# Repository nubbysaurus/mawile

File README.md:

# mawile
Testing the limits of a single I<sup>2</sup>C bus.

## updates
* MKII : separating ADCs into a single boards / ADC; see eevee for more information.

## summary
This repo contains KiCad EDA files related to a RaspberryPi 3 Model B shield that 
will test the number of devices that a single Pi I<sup>2</sup>C bus can reach.

* x4 3.3V I<sup>2</sup>C connectors

## to-do
* include other interfaces (SPI, UART, etc)

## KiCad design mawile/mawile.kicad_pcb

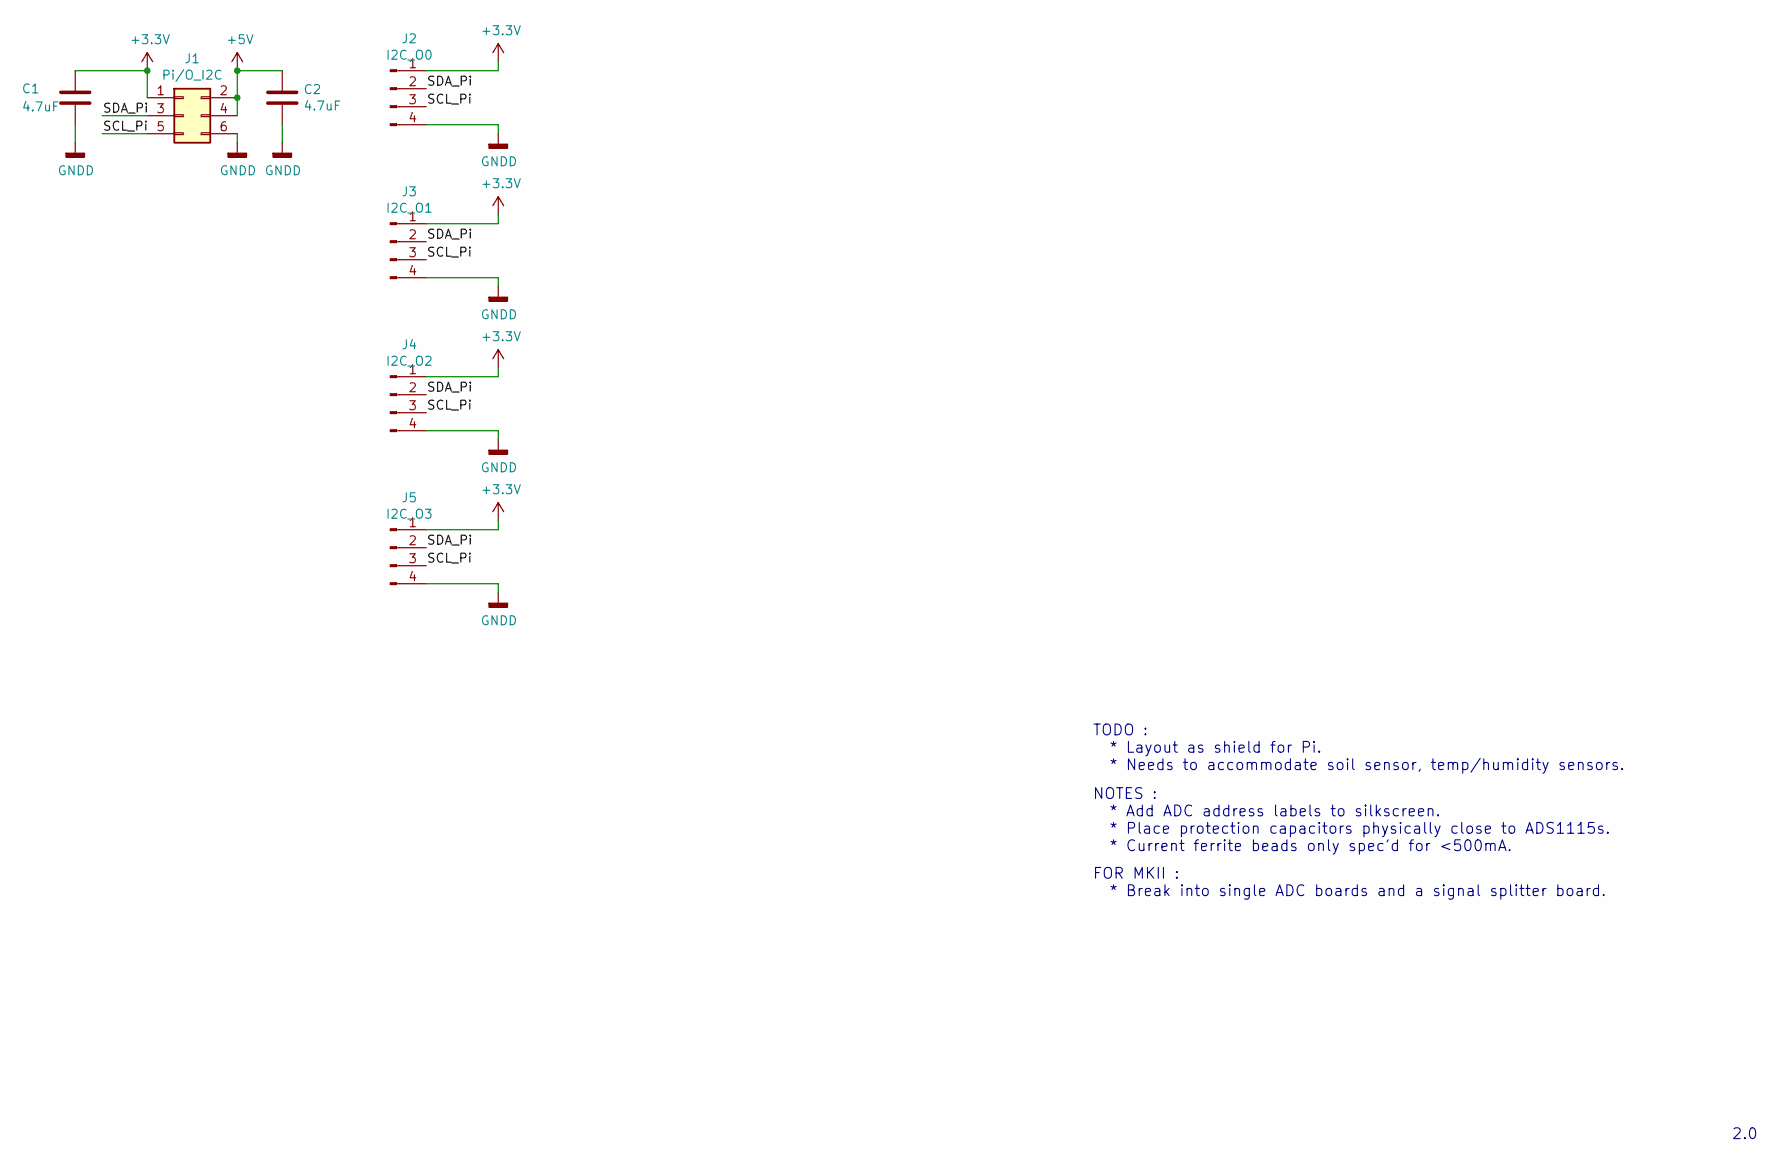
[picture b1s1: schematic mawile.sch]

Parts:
C1, C2: 4.7uF; C_0805_2012Metric_Pad1.15x1.40mm_HandSolder
J1: Pi/O_I2C; PinHeader_2x03_P2.54mm_Vertical
J2: I2C_O0; PinHeader_1x04_P2.54mm_Vertical
J3: I2C_O1; PinHeader_1x04_P2.54mm_Vertical
J4: I2C_O2; PinHeader_1x04_P2.54mm_Vertical
J5: I2C_O3; PinHeader_1x04_P2.54mm_Vertical

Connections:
+3V3: C1.1, J1.1, J2.1, J3.1, J4.1, J5.1
+5V: C2.1, J1.2, J1.4
/SCL_Pi: J1.5, J2.3, J3.3, J4.3, J5.3
/SDA_Pi: J1.3, J2.2, J3.2, J4.2, J5.2
GNDD: C1.2, C2.2, J1.6, J2.4, J3.4, J4.4, J5.4

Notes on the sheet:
NOTES : * Add ADC address labels to silkscreen. * Place protection capacitors physically close to ADS1115s. * Current ferrite beads only spec'd for <500mA.
TODO : * Layout as shield for Pi. * Needs to accommodate soil sensor, temp/humidity sensors.
FOR MKII : * Break into single ADC boards and a signal splitter board.
2.0

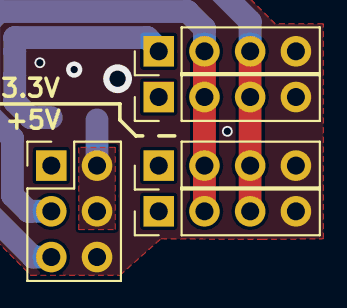
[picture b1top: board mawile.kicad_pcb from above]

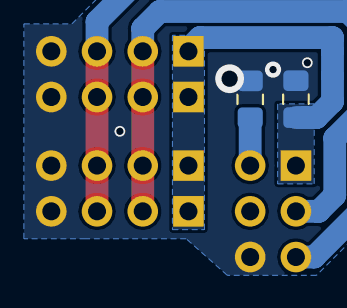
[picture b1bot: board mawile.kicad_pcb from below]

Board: 2 copper layers, 7 parts (2 on the bottom side), 5 nets.

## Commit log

2020-06-19 switched old sableye to real mawile
2020-07-01 added some more docs
2020-07-01 TODO added
2020-07-01 revised progress, to-do
2020-07-01 v2.0 schematic - outputs; may remove second buffer
